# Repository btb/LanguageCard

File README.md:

# LanguageCard
 An Apple II Language Card. Based on a design by [iz8dwf](https://youtu.be/1KPIAoO1dTU)

[Interactive BOM](https://btb.github.io/LanguageCard/bom/LanguageCard_3.html)

## Description

This is a simple "language card" for the Apple II and II+, which expands the system from 48K to 64K by means of 16K of RAM, switchable into the address space normally used by the system firmware. That's two banks of 4K in the D0-D8 space, and one bank of 8K in the E0-F8 space. The C0-C8 space is not touched.

It uses static RAM so there is no need for the ribbon cable connecting it to the logic board that the original language cards had.

Like the original language cards, it can also contain a chip that will be used to replace the F8 ROM on your logic board. Additionally, you can enable or disable this replacement ROM with a switch or jumpers. If configured correctly, you can put two different F8 ROM images on a single chip and switch back and forth between them.

## Build Notes

### R3, R4, R5

Use higher resistance for	high-efficiency LEDs, e.g. 3.3K

### U8 and U9

Any narrow 8KBx8	static RAM can be used.	ex: 5C6408, Cy7C185, TC5588

### U7

Optional. 2K or larger	(E)EPROM for overriding the	logic board's F8 ROM. Enable	using SW1 or JP1.

### SW1

Optional Toggle switch. Miniature, Sub-miniature, or Ultra-miniature, right angle, SPDT. (Sub, Ultra-mini use JP1 pads)

An SPST switch which only closes the outer two pin positions can also work if you short JP3. 

To switch between two different F8 ROM images on a single 4K or greater chip, short JP2 and use a	DPDT switch instead - must be a three-position center OFF switch (ON-OFF-ON) in order to disable the card ROM and use the logic board F8 ROM.

### JP1

Enable and select which F8 ROM to use (if not using SW1)

| | |
|-|-|
|6|5|
|4|3|
|2|1|

No Jumpers: Card ROM disabled

#### Using a single ROM image:

JP2 open, Jumper on pins 1,3 (lower right): Card ROM enabled

#### Using two ROM images on a 4K or larger ROM:

JP2 shorted, Jumper on pins 1,3 (lower right) and 2,4 (lower left): Upper ROM image enabled (A11 high)

JP2 shorted, Jumper on pins 3,5 (upper right) and 4,6 (upper left): Lower ROM image enabled (A11 low)

### Solder Jumper JP2
Short, and install DPDT switch	(or use pair of jumpers as above) for	ability to select two different F8	ROM images on a single (4K or larger) ROM. 

### Solder Jumper JP3
Short if using an SPST switch	that only connects outer two pins

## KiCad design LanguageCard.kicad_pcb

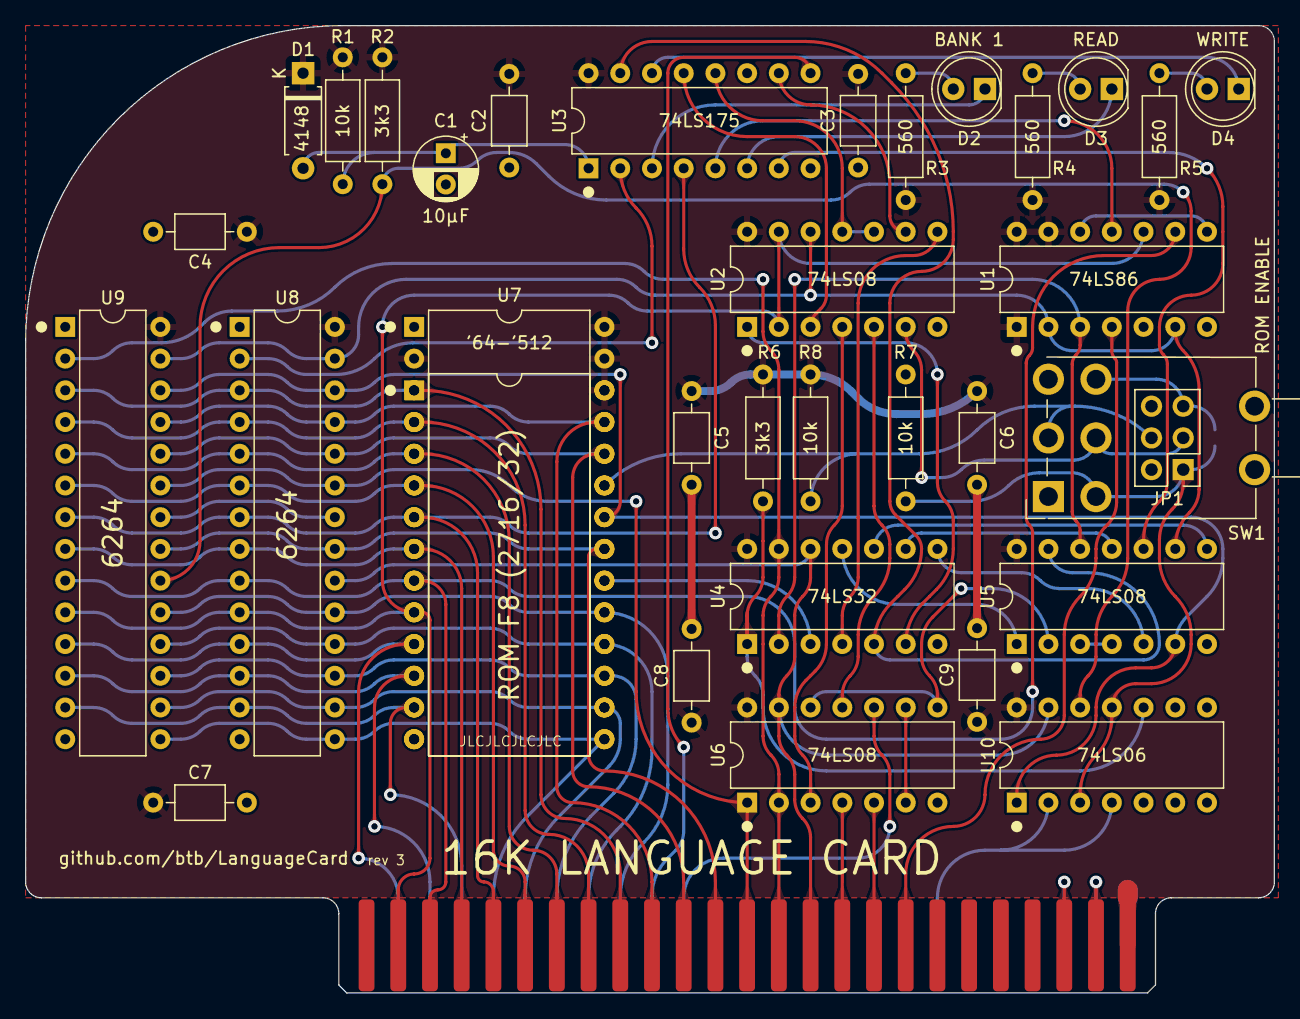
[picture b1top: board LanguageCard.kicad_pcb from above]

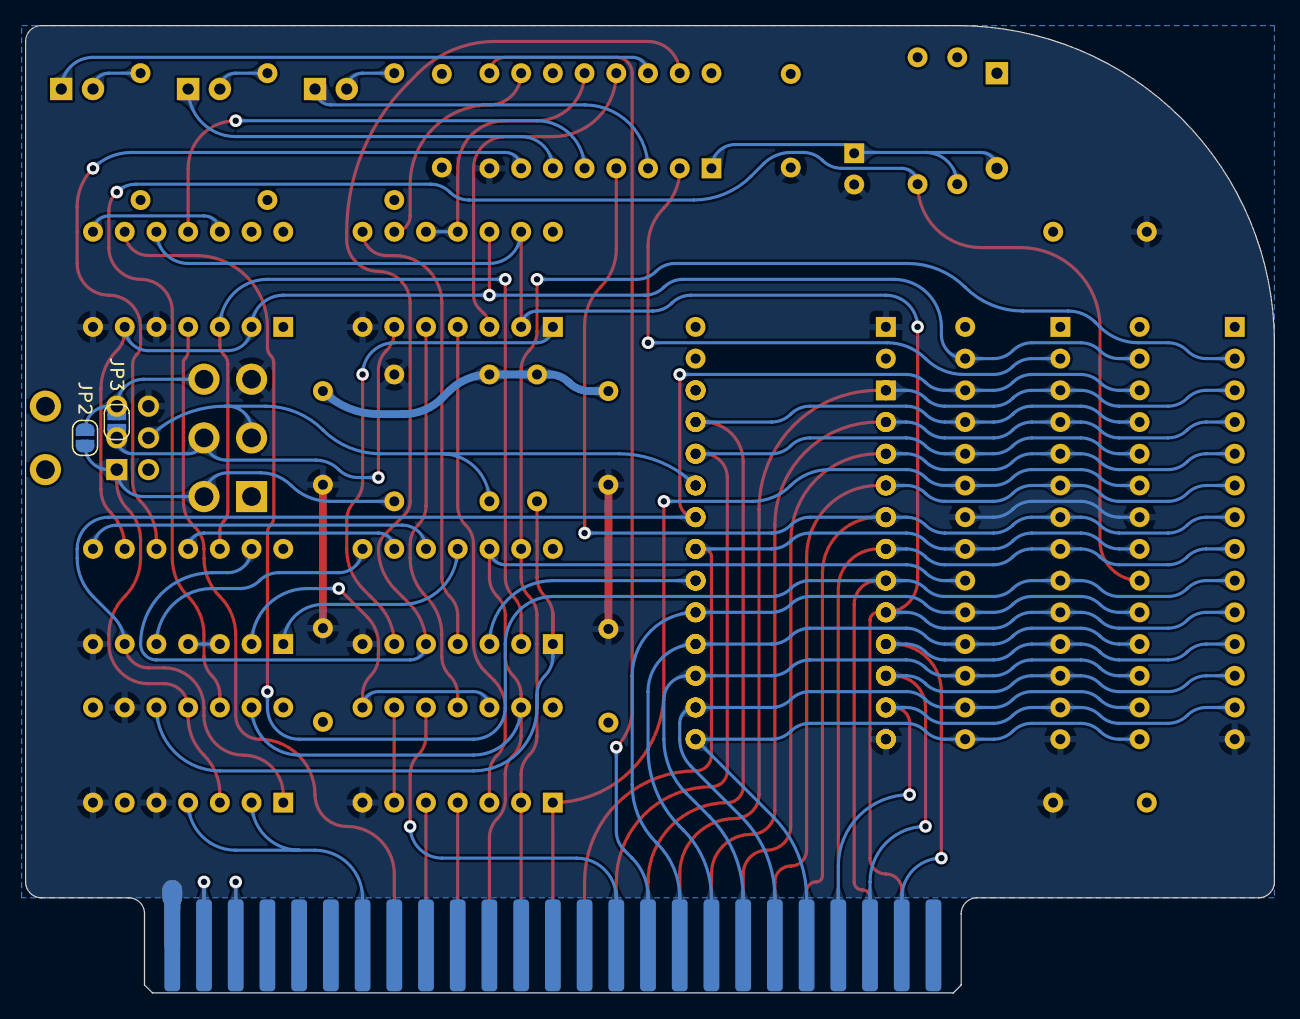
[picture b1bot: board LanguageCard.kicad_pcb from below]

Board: 2 copper layers, 100.0 x 77.5 mm, 37 parts (2 on the bottom side), 68 nets.

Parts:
C1: 10μF; CP_Radial_D5.0mm_P2.50mm
C2, C3, C4, C5, C6, C7, C8, C9: 100n; C_Axial_L3.8mm_D2.6mm_P7.50mm_Horizontal
D1: 4148; D_A-405_P7.62mm_Horizontal
D2: BANK 1; LED_D5.0mm
D3: READ; LED_D5.0mm
D4: WRITE; LED_D5.0mm
J1: Apple II Expansion Bus; Apple II Expansion Edge Connector
JP1: ROM Enable; PinHeader_2x03_P2.54mm_Vertical
JP2: DUAL ROM; SolderJumper-2_P1.3mm_Open_RoundedPad1.0x1.5mm
JP3: SPST; SolderJumper-2_P1.3mm_Open_RoundedPad1.0x1.5mm
R1, R7, R8: 10k; R_Axial_DIN0207_L6.3mm_D2.5mm_P10.16mm_Horizontal
R2, R6: 3k3; R_Axial_DIN0207_L6.3mm_D2.5mm_P10.16mm_Horizontal
R3, R4, R5: 560; R_Axial_DIN0207_L6.3mm_D2.5mm_P10.16mm_Horizontal
SW1: ROM ENABLE; SW_Lever_2P2T_Alcoswitch_AE203SD1
U1: 74LS86; DIP-14_W7.62mm
U2, U5, U6: 74LS08; DIP-14_W7.62mm
U3: 74LS175; DIP-16_W7.62mm
U4: 74LS32; DIP-14_W7.62mm
U7: ROM F8 (2716/32); DIP-24_W15.24mm
U7Alt1: '64-'512; DIP-28_W15.24mm
U8, U9: 6264; DIP-28_W7.62mm
U10: 74LS06; DIP-14_W7.62mm

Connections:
+5V: C2.2, C3.2, C4.1, C5.1, C6.1, C7.1, C8.1, C9.1, D1.1 (K), J1.25, R1.1, R2.2, R3.2, R4.2, R5.2, R6.2, R8.2, U1.1, U1.13, U1.14 (VCC), U2.14 (VCC), U3.16 (VCC), U4.14 (VCC), U5.14 (VCC), U6.14 (VCC), U7.24 (VCC), U7Alt1.2 (A12), U7Alt1.26 (A13/NC), U7Alt1.27 (A14/~WE), U7Alt1.28 (VCC), U8.28 (VCC), U9.28 (VCC), U10.14 (VCC)
/A0: J1.2, U1.10, U2.2, U2.13, U7.8 (A0), U7Alt1.10 (A0), U8.10 (A0), U9.10 (A0)
/A1: J1.3, U1.9, U7.7 (A1), U7Alt1.9 (A1), U8.9 (A1), U9.9 (A1)
/A2: J1.4, U7.6 (A2), U7Alt1.8 (A2), U8.8 (A2), U9.8 (A2)
/A3: J1.5, U3.4 (D0), U7.5 (A3), U7Alt1.7 (A3), U8.7 (A3), U9.7 (A3)
/A4: J1.6, U7.4 (A4), U7Alt1.6 (A4), U8.6 (A4), U9.6 (A4)
/A5: J1.7, U7.3 (A5), U7Alt1.5 (A5), U8.5 (A5), U9.5 (A5)
/A6: J1.8, U7.2 (A6), U7Alt1.4 (A6), U8.4 (A6), U9.4 (A6)
/A7: J1.9, U7.1 (A7), U7Alt1.3 (A7), U8.3 (A7), U9.3 (A7)
/A8: J1.10, U7.23 (A8), U7Alt1.25 (A8), U8.25 (A8), U9.25 (A8)
/A9: J1.11, U7.22 (A9), U7Alt1.24 (A9), U8.24 (A9), U9.24 (A9)
/A10: J1.12, U7.19 (A10), U7Alt1.21 (A10), U8.21 (A10), U9.21 (A10)
/A11: J1.13, U6.1, U8.23 (A11), U9.23 (A11)
/A12: J1.14, U4.13, U6.2, U9.2 (A12)
/A13: J1.15, U4.12, U6.13, U8.20 (~CE), U10.13
/A14: J1.16, U6.4
/A15: J1.17, U6.5
/ABNK: U3.2 (Q0), U8.2 (A12)
/BR/W: U1.2, U1.6, U2.12, U5.9, U8.27 (~WE), U9.27 (~WE)
/D0: J1.49, U7.9 (D0), U7Alt1.11 (D0), U8.11 (Q0), U9.11 (Q0)
/D1: J1.48, U7.10 (D1), U7Alt1.12 (D1), U8.12 (Q1), U9.12 (Q1)
/D2: J1.47, U7.11 (D2), U7Alt1.13 (D2), U8.13 (Q2), U9.13 (Q2)
/D3: J1.46, U7.13 (D3), U7Alt1.15 (D3), U8.15 (Q3), U9.15 (Q3)
/D4: J1.45, U7.14 (D4), U7Alt1.16 (D4), U8.16 (Q4), U9.16 (Q4)
/D5: J1.44, U7.15 (D5), U7Alt1.17 (D5), U8.17 (Q5), U9.17 (Q5)
/D6: J1.43, U7.16 (D6), U7Alt1.18 (D6), U8.18 (Q6), U9.18 (Q6)
/D7: J1.42, U7.17 (D7), U7Alt1.19 (D7), U8.19 (Q7), U9.19 (Q7)
/DFP: U5.3, U5.4
/F8SEL: JP1.3, JP3.1 (A), SW1.5 (B), U2.6
/NEXT: U2.9, U3.10 (Q2)
/PHI0: J1.40, U6.10
/RAMCE: U5.6, U7.20 (~OE), U7Alt1.22 (~OE), U8.26 (CE2), U9.26 (CE2), U10.1
/RAMEN: U3.7 (Q1), U5.10
/ROMA11/VPP/~WE: JP1.4, R8.1, SW1.2 (B), U7.21 (VPP), U7Alt1.23 (A11)
/ROMEN: JP1.1, JP2.2 (B), R7.2, SW1.4 (A), U10.3, U10.11
/ROMEN2: JP1.5, JP2.1 (A), JP3.2 (B), SW1.6 (C)
/R/W: J1.18, U1.4
/WE: U3.15 (Q3), U4.5, U5.13
/~A13: R2.1, U9.20 (~CE), U10.12
/~ABNK: D2.1 (K), U3.3 (~Q0)
/~DEV: J1.41, U3.9 (Cp)
/~INH: J1.32, U10.2, U10.4
/~RAMEN: D3.1 (K), U3.6 (~Q1)
/~RESET: C1.1, D1.2 (A), R1.2, U3.1 (~Mr)
/~ROMCE: U4.3, U7.18 (~CE/PGM), U7Alt1.20 (~CE)
/~R/W: U1.3, U4.2, U5.12
/~WE: D4.1 (K), U3.14 (~Q3)
GND: C1.2, C2.1, C3.1, C4.2, C5.2, C6.2, C7.2, C8.2, C9.2, J1.26, JP1.6, R7.1, SW1.3 (C), U1.5, U1.7 (GND), U2.7 (GND), U3.8 (GND), U4.7 (GND), U5.7 (GND), U6.7 (GND), U7.12 (GND), U7Alt1.1 (A15/~BSY), U7Alt1.14 (GND), U8.14 (GND), U8.22 (~OE), U9.14 (GND), U9.22 (~OE), U10.5, U10.7 (GND), U10.9
unnamed: D2.2 (A), R3.1
unnamed: D3.2 (A), R4.1
unnamed: D4.2 (A), R5.1
unnamed: J1.23, J1.28
unnamed: J1.24, J1.27
unnamed: R6.1, U4.1, U10.10
unnamed: U1.8, U1.12
unnamed: U2.1, U4.6
unnamed: U2.4, U6.3
unnamed: U2.5, U6.11
unnamed: U2.8, U4.4
unnamed: U1.11, U3.5 (D1)
unnamed: U2.10, U2.11, U3.12 (D2)
unnamed: U2.3, U3.13 (D3)
unnamed: U4.8, U5.5
unnamed: U4.9, U5.11
unnamed: U4.10, U5.8
unnamed: U4.11, U5.1
unnamed: U5.2, U6.8, U6.12
unnamed: U6.6, U6.9

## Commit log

2022-08-03 Add KiCad files
2022-08-03 add schematic pdf and gerber files
2022-08-06 Add interactive BOM
2022-08-07 Update BOM
2022-09-29 support larger SRAMS, minor updates
2022-10-08 no, 32kx8 does not work. need two chip selects
2022-10-08 add teardrops
2022-10-08 fix up silkscreens and fabs
2022-10-10 mark rev 0
2022-10-10 cleanup
2022-10-10 update pdf
2022-10-10 update symbols
2022-10-10 use kibot config file
2022-10-10 fix filename
2022-10-10 have kibot run checks
2022-10-10 also check parity
2022-10-10 looks like dev version required for parity check
2022-10-10 doesn't really work that well yet
2022-10-10 just use a generic connector
2023-08-30 update to Kicad 7
2023-09-01 Larger ROM, enable switch
2023-09-02 dual rom config, lots of tweaks
2023-09-02 jlcpcb settings
2023-09-02 rev 2 gerbers
2023-09-02 rev2 BOM
2023-09-04 add switch model and render
2023-09-21 rev 3
2023-09-21 correct image
